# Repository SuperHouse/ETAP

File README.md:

SuperHouse Automation Electronic Tap Controller
===============================================

Copyright 2015 SuperHouse Automation Pty Ltd  
SuperHouse site:  www.superhouse.tv  
SuperHouse email: info@superhouse.tv  

Arduino-compatible board designed to be a drop-in replacement for the
Ryemetal "Hotshot" electronic tap controller. Maintains the same physical
layout including position of LEDs and the main connector.

Features:

 * ATmega328P MCU
 * Arduino R3 headers
 * 5V and 3.3V voltage regulators
 * 3 x N-channel MOSFETs for controlling cold, warm, and hot water solenoids
 * 5 x status LEDs for cold, warm, hot, long, and short
 * Serial header in FTDI format

More information is available at:

  http://www.superhouse.tv/etap

INSTALLATION
------------
The design is saved as an EAGLE project. EAGLE PCB design software is
available from www.cadsoftusa.com free for non-commercial use. To use
this project download it and place the directory containing these files
into the "eagle" directory on your computer.

DISTRIBUTION
------------
The specific terms of distribution of this project are governed by the
license referenced below.

LICENSE
-------
Licensed under the TAPR Open Hardware License (www.tapr.org/OHL).
The "license" folder within this repository also contains a copy of
this license in plain text format.

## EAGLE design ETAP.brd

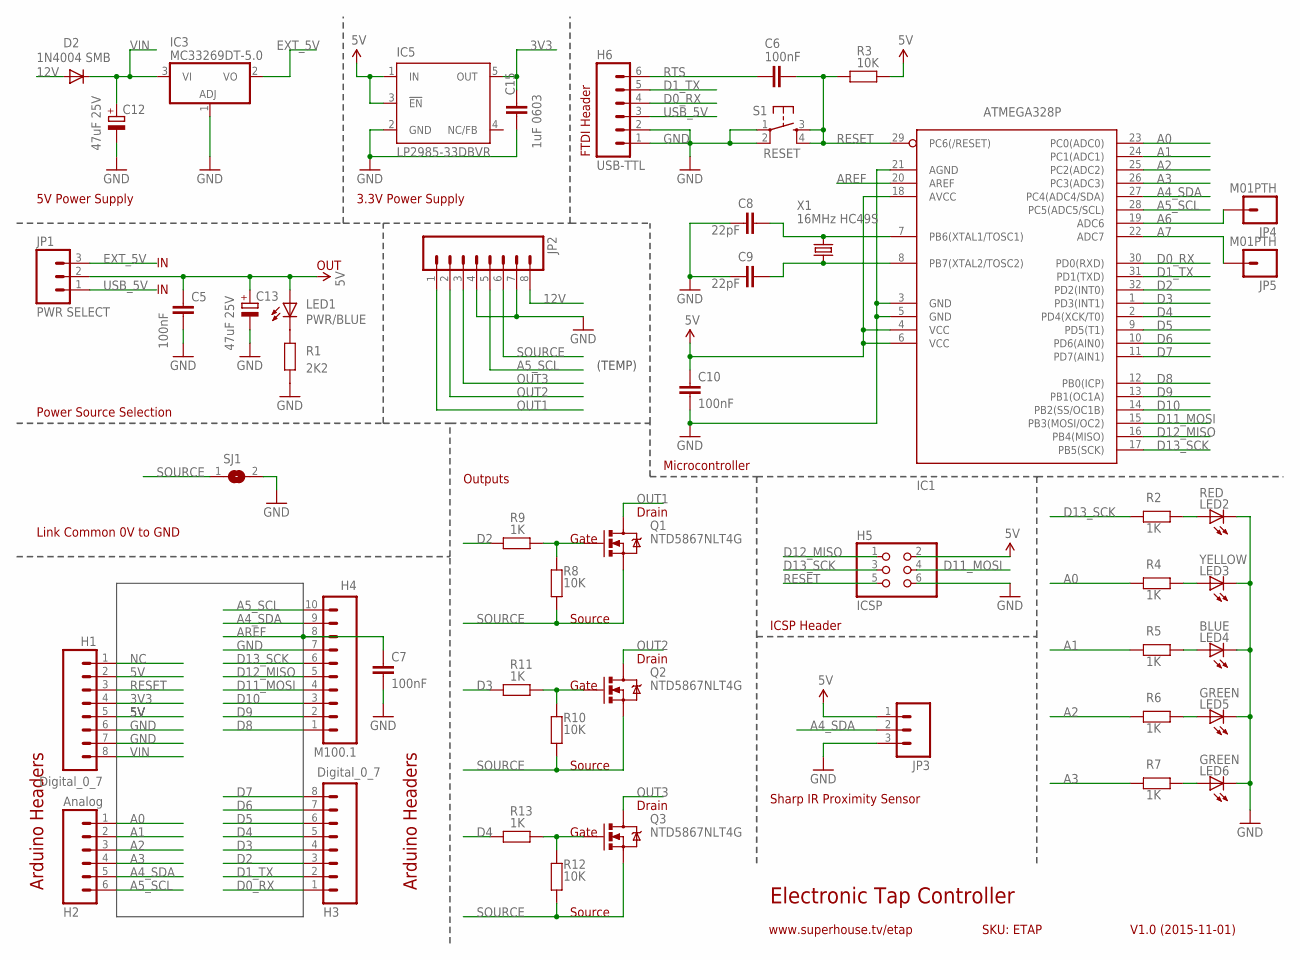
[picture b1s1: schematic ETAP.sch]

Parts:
C5, C6, C7, C10: 100nF; 0603
C8, C9: 22pF; 0603
C12, C13: 47uF 25V; PANASONIC_D
C15: 1uF 0603; 0603
D2: 1N4004 SMB; SMB-DIODE
H1, H3: Digital_0_7; 1X08
H2: Analog; 1X06
H4: M100.1; 1X10
H5: ICSP; 2X03
H6: USB-TTL; 1X06
IC1: ATMEGA328P; TQFP32-08
IC3: MC33269DT-5.0; DPACK
IC5: LP2985-33DBVR; TEXAS_SOT23-DBV
JP1: PWR SELECT; 1X03
JP2: M08STD; 1X08
JP3: M03PTH; 1X03
JP4, JP5: M01PTH; 1X01
LED1: PWR/BLUE; LED-0603
LED2: RED; LED3MM
LED3: YELLOW; LED3MM
LED4: BLUE; LED3MM
LED5, LED6: GREEN; LED3MM
Q1, Q2, Q3: NTD5867NLT4G; DPACK
R1: 2K2; 0603
R2, R4, R5, R6, R7, R9, R11, R13: 1K; 0603
R3, R8, R10, R12: 10K; 0603
S1: RESET; TACTILE-PTH
SJ1: SJ
X1: 16MHz HC49S; HC49U-V

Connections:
3V3: C15.2, H1.4, IC5.5 (OUT)
5V: C5.1, C10.1, C13.+, H1.2, H1.5, H5.2, IC1.4 (VCC), IC1.6 (VCC), IC1.18 (AVCC), IC5.1 (IN), IC5.3 (!EN), JP1.2, JP3.1, LED1.A, R3.2
12V: D2.A, JP2.8
A0: H2.1, IC1.23 (PC0(ADC0)), R4.2
A1: H2.2, IC1.24 (PC1(ADC1)), R5.2
A2: H2.3, IC1.25 (PC2(ADC2)), R6.2
A3: H2.4, IC1.26 (PC3(ADC3)), R7.2
A4_SDA: H2.5, H4.9, IC1.27 (PC4(ADC4/SDA)), JP3.2
A5_SCL: H2.6, H4.10, IC1.28 (PC5(ADC5/SCL)), JP2.5
A6: IC1.19 (ADC6), JP4.1
A7: IC1.22 (ADC7), JP5.1
AREF: C7.1, H4.8, IC1.20 (AREF)
D0_RX: H3.1, H6.4, IC1.30 (PD0(RXD))
D1_TX: H3.2, H6.5, IC1.31 (PD1(TXD))
D2: H3.3, IC1.32 (PD2(INT0)), R9.2
D3: H3.4, IC1.1 (PD3(INT1)), R11.2
D4: H3.5, IC1.2 (PD4(XCK/T0)), R13.2
D5: H3.6, IC1.9 (PD5(T1))
D6: H3.7, IC1.10 (PD6(AIN0))
D7: H3.8, IC1.11 (PD7(AIN1))
D8: H4.1, IC1.12 (PB0(ICP))
D9: H4.2, IC1.13 (PB1(OC1A))
D10: H4.3, IC1.14 (PB2(SS/OC1B))
D11_MOSI: H4.4, H5.4, IC1.15 (PB3(MOSI/OC2))
D12_MISO: H4.5, H5.1, IC1.16 (PB4(MISO))
D13_SCK: H4.6, H5.3, IC1.17 (PB5(SCK)), R2.2
EXT_5V: IC3.2 (VO), JP1.3
GND: C5.2, C7.2, C8.1, C9.1, C10.2, C12.-, C13.-, C15.1, H1.6, H1.7, H4.7, H5.6, H6.1, H6.2, IC1.3 (GND), IC1.5 (GND), IC1.21 (AGND), IC3.1 (ADJ), IC5.2 (GND), JP2.4, JP2.7, JP3.3, LED2.K (C), LED3.K (C), LED4.K (C), LED5.K (C), LED6.K (C), R1.1, S1.1, S1.2, SJ1.2
unnamed: Q2.1 (G), R10.2, R11.1
unnamed: LED2.A, R2.1
unnamed: Q1.1 (G), R8.2, R9.1
unnamed: Q3.1 (G), R12.2, R13.1
unnamed: C8.2, IC1.7 (PB6(XTAL1/TOSC1)), X1.2
unnamed: C9.2, IC1.8 (PB7(XTAL2/TOSC2)), X1.1
unnamed: LED3.A, R4.1
unnamed: LED4.A, R5.1
unnamed: LED5.A, R6.1
unnamed: LED6.A, R7.1
unnamed: LED1.C, R1.2
NC: H1.1
OUT1: JP2.1, Q1.2 (D)
OUT2: JP2.2, Q2.2 (D)
OUT3: JP2.3, Q3.2 (D)
RESET: C6.2, H1.3, H5.5, IC1.29 (PC6(/RESET)), R3.1, S1.3, S1.4
RTS: C6.1, H6.6
SOURCE: JP2.6, Q1.3 (S), Q2.3 (S), Q3.3 (S), R8.1, R10.1, R12.1, SJ1.1
USB_5V: H6.3, JP1.1
VIN: C12.+, D2.C, H1.8, IC3.3 (VI)

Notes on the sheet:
Electronic Tap Controller
V1.0 (2015-11-01)
SKU: ETAP
www.superhouse.tv/etap
5V Power Supply
Power Source Selection
Arduino Headers
ICSP Header
Microcontroller
OUT
FTDI Header
Drain
Gate
Source
Sharp IR Proximity Sensor
3.3V Power Supply
Link Common 0V to GND
Outputs
(TEMP)

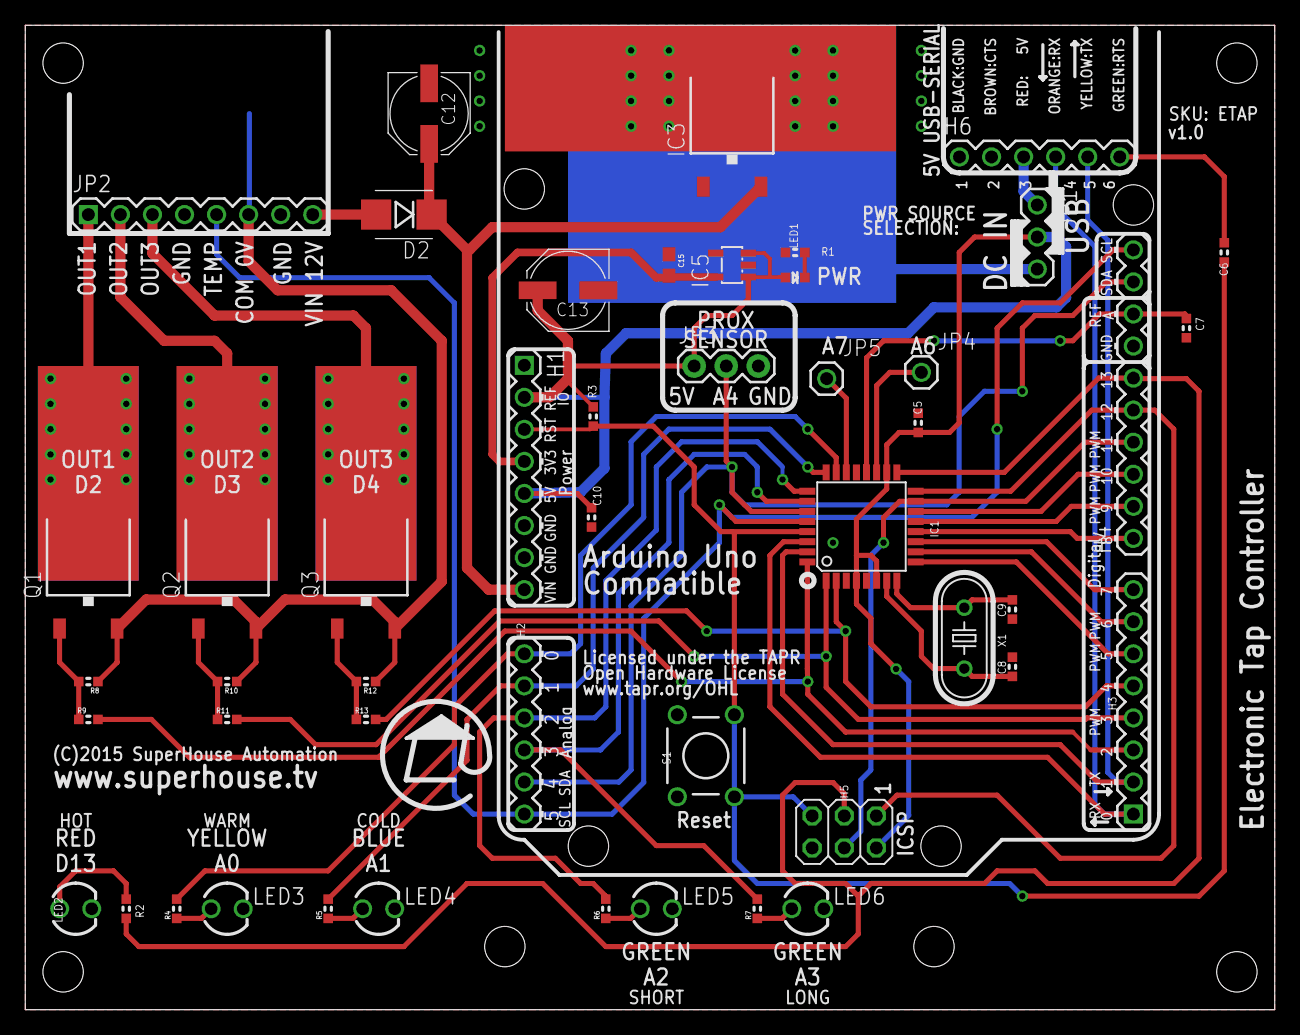
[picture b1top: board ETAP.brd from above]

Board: 2 copper layers, 99.0 x 78.0 mm, 49 parts (1 on the bottom side), 47 nets.

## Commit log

2016-04-24 Initial import for v1.0 release

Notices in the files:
ETAP.brd:
(C)2015 SuperHouse Automation
parts and their libraries:
freetronics-marc: Licensing: CC v3.0 Share-Alike You are welcome to use this library for commercial purposes.
